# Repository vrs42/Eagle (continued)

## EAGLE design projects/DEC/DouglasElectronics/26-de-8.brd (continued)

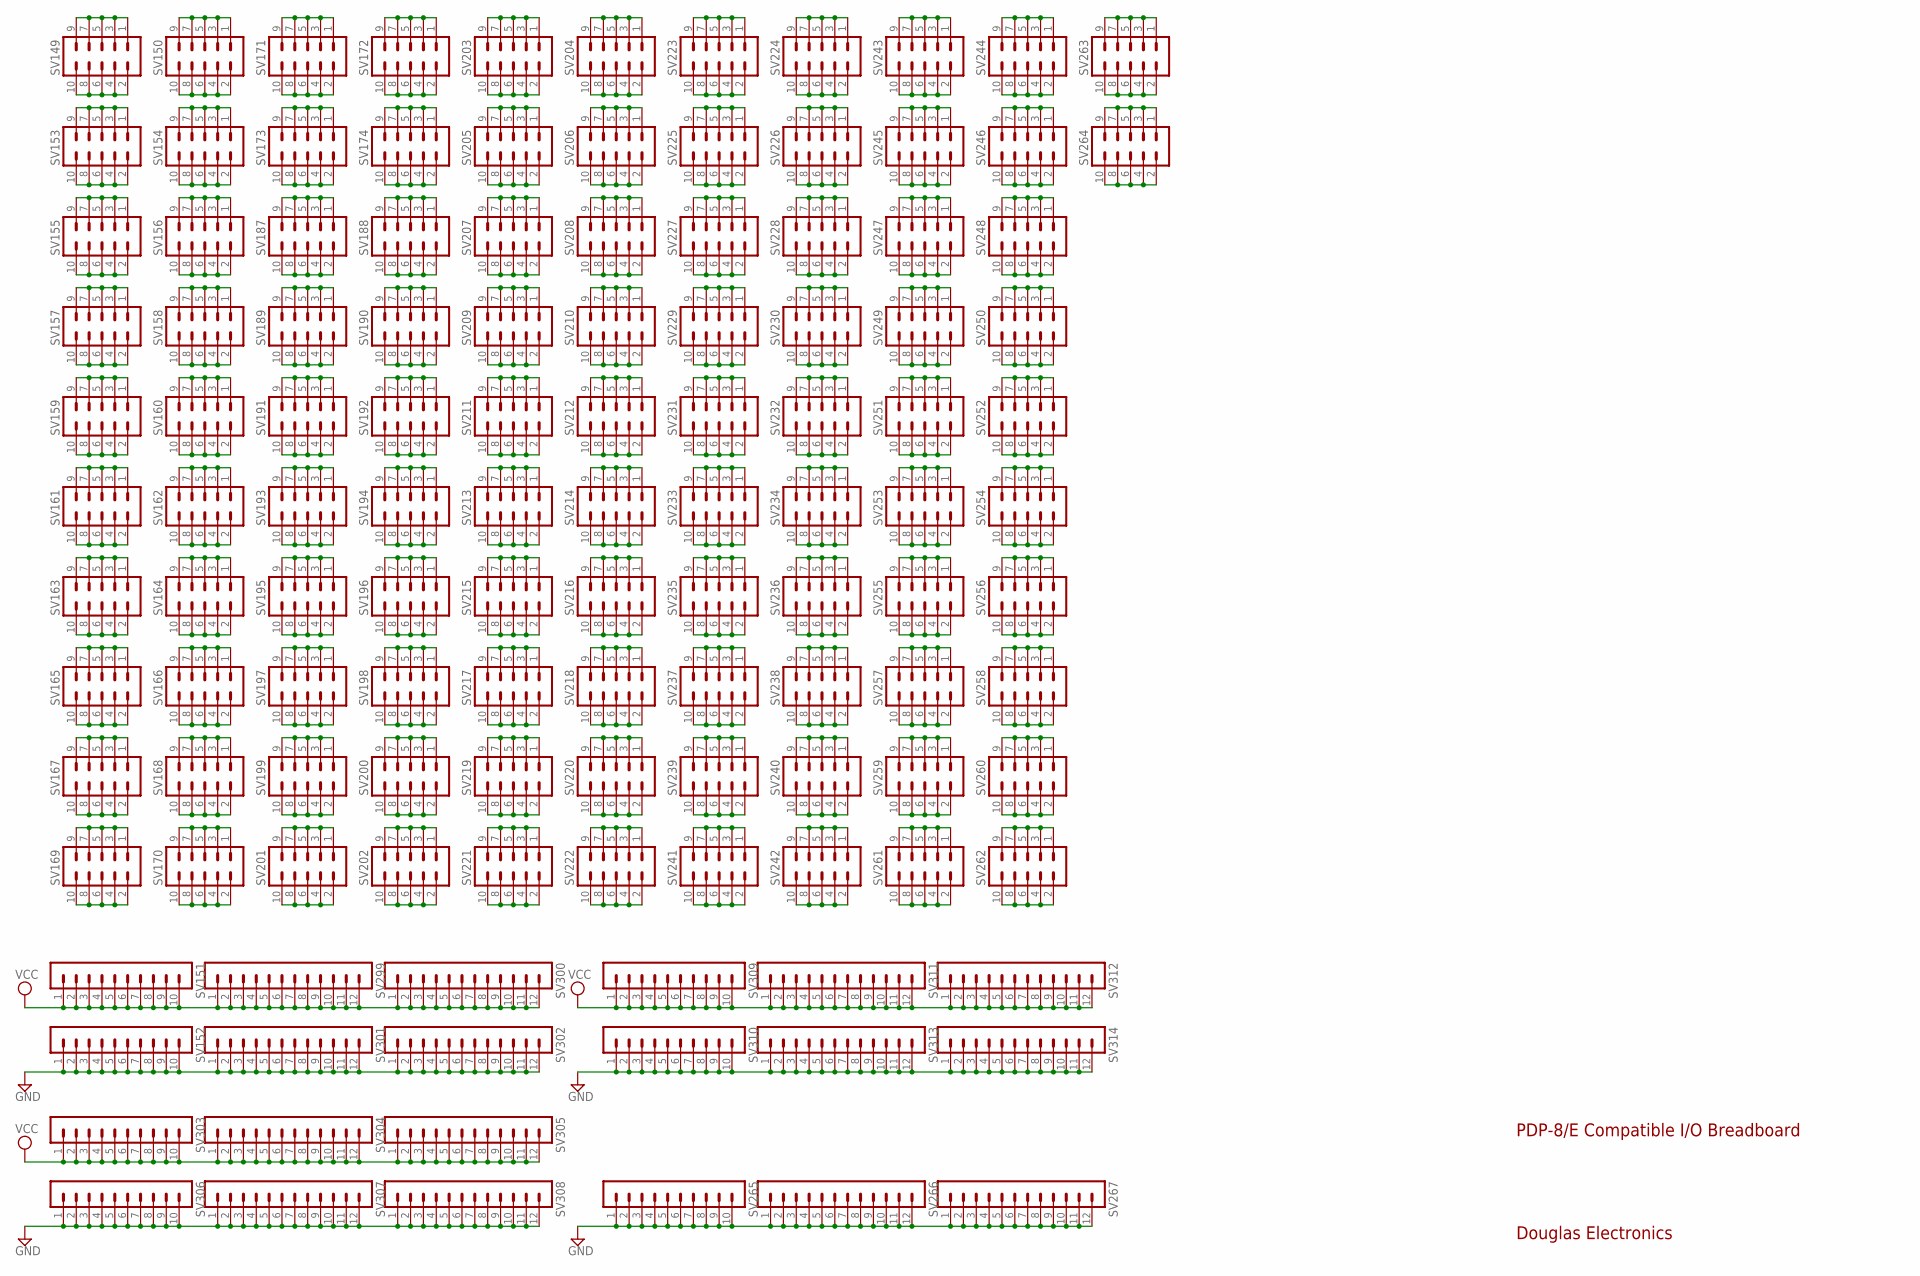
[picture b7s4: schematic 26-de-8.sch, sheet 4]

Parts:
SV149, SV150, SV153, SV154, SV155, SV156, SV157, SV158, SV159, SV160, SV161, SV162, SV163, SV164, SV165, SV166, SV167, SV168, SV169, SV170, SV171, SV172, SV173, SV174, SV187, SV188, SV189, SV190, SV191, SV192, SV193, SV194, SV195, SV196, SV197, SV198, SV199, SV200, SV201, SV202, SV203, SV204, SV205, SV206, SV207, SV208, SV209, SV210, SV211, SV212, SV213, SV214, SV215, SV216, SV217, SV218, SV219, SV220, SV221, SV222, SV223, SV224, SV225, SV226, SV227, SV228, SV229, SV230, SV231, SV232, SV233, SV234, SV235, SV236, SV237, SV238, SV239, SV240, SV241, SV242, SV243, SV244, SV245, SV246, SV247, SV248, SV249, SV250, SV251, SV252, SV253, SV254, SV255, SV256, SV257, SV258, SV259, SV260, SV261, SV262, SV263, SV264: MA05-2
SV151, SV152, SV265, SV303, SV306, SV309, SV310: MA10-1
SV266, SV267, SV299, SV300, SV301, SV302, SV304, SV305, SV307, SV308, SV311, SV312, SV313, SV314: MA12-1

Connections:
GND: SV152.1, SV152.2, SV152.3, SV152.4, SV152.5, SV152.6, SV152.7, SV152.8, SV152.9, SV152.10, SV265.1, SV265.2, SV265.3, SV265.4, SV265.5, SV265.6, SV265.7, SV265.8, SV265.9, SV265.10, SV266.1, SV266.2, SV266.3, SV266.4, SV266.5, SV266.6, SV266.7, SV266.8, SV266.9, SV266.10, SV266.11, SV266.12, SV267.1, SV267.2, SV267.3, SV267.4, SV267.5, SV267.6, SV267.7, SV267.8, SV267.9, SV267.10, SV267.11, SV267.12, SV301.1, SV301.2, SV301.3, SV301.4, SV301.5, SV301.6, SV301.7, SV301.8, SV301.9, SV301.10, SV301.11, SV301.12, SV302.1, SV302.2, SV302.3, SV302.4, SV302.5, SV302.6, SV302.7, SV302.8, SV302.9, SV302.10, SV302.11, SV302.12, SV306.1, SV306.2, SV306.3, SV306.4, SV306.5, SV306.6, SV306.7, SV306.8, SV306.9, SV306.10, SV307.1, SV307.2, SV307.3, SV307.4, SV307.5, SV307.6, SV307.7, SV307.8, SV307.9, SV307.10, SV307.11, SV307.12, SV308.1, SV308.2, SV308.3, SV308.4, SV308.5, SV308.6, SV308.7, SV308.8, SV308.9, SV308.10, SV308.11, SV308.12, SV310.1, SV310.2, SV310.3, SV310.4, SV310.5, SV310.6, SV310.7, SV310.8, SV310.9, SV310.10, SV313.1, SV313.2, SV313.3, SV313.4, SV313.5, SV313.6, SV313.7, SV313.8, SV313.9, SV313.10, SV313.11, SV313.12, SV314.1, SV314.2, SV314.3, SV314.4, SV314.5, SV314.6, SV314.7, SV314.8, SV314.9, SV314.10, SV314.11, SV314.12; also elsewhere on the board
unnamed: SV149.1, SV149.3, SV149.5, SV149.7, SV149.9
unnamed: SV149.2, SV149.4, SV149.6, SV149.8, SV149.10
unnamed: SV150.1, SV150.3, SV150.5, SV150.7, SV150.9
unnamed: SV150.2, SV150.4, SV150.6, SV150.8, SV150.10
unnamed: SV153.1, SV153.3, SV153.5, SV153.7, SV153.9
unnamed: SV153.2, SV153.4, SV153.6, SV153.8, SV153.10
unnamed: SV154.1, SV154.3, SV154.5, SV154.7, SV154.9
unnamed: SV154.2, SV154.4, SV154.6, SV154.8, SV154.10
unnamed: SV155.1, SV155.3, SV155.5, SV155.7, SV155.9
unnamed: SV155.2, SV155.4, SV155.6, SV155.8, SV155.10
unnamed: SV156.1, SV156.3, SV156.5, SV156.7, SV156.9
unnamed: SV156.2, SV156.4, SV156.6, SV156.8, SV156.10
unnamed: SV157.1, SV157.3, SV157.5, SV157.7, SV157.9
unnamed: SV157.2, SV157.4, SV157.6, SV157.8, SV157.10
unnamed: SV158.1, SV158.3, SV158.5, SV158.7, SV158.9
unnamed: SV158.2, SV158.4, SV158.6, SV158.8, SV158.10
unnamed: SV159.1, SV159.3, SV159.5, SV159.7, SV159.9
unnamed: SV159.2, SV159.4, SV159.6, SV159.8, SV159.10
unnamed: SV160.1, SV160.3, SV160.5, SV160.7, SV160.9
unnamed: SV160.2, SV160.4, SV160.6, SV160.8, SV160.10
unnamed: SV161.1, SV161.3, SV161.5, SV161.7, SV161.9
unnamed: SV161.2, SV161.4, SV161.6, SV161.8, SV161.10
unnamed: SV162.1, SV162.3, SV162.5, SV162.7, SV162.9
unnamed: SV162.2, SV162.4, SV162.6, SV162.8, SV162.10
unnamed: SV163.1, SV163.3, SV163.5, SV163.7, SV163.9
unnamed: SV163.2, SV163.4, SV163.6, SV163.8, SV163.10
unnamed: SV164.1, SV164.3, SV164.5, SV164.7, SV164.9
unnamed: SV164.2, SV164.4, SV164.6, SV164.8, SV164.10
unnamed: SV165.1, SV165.3, SV165.5, SV165.7, SV165.9
unnamed: SV165.2, SV165.4, SV165.6, SV165.8, SV165.10
unnamed: SV166.1, SV166.3, SV166.5, SV166.7, SV166.9
unnamed: SV166.2, SV166.4, SV166.6, SV166.8, SV166.10
unnamed: SV167.1, SV167.3, SV167.5, SV167.7, SV167.9
unnamed: SV167.2, SV167.4, SV167.6, SV167.8, SV167.10
unnamed: SV168.1, SV168.3, SV168.5, SV168.7, SV168.9
unnamed: SV168.2, SV168.4, SV168.6, SV168.8, SV168.10
unnamed: SV169.1, SV169.3, SV169.5, SV169.7, SV169.9
unnamed: SV169.2, SV169.4, SV169.6, SV169.8, SV169.10
unnamed: SV170.1, SV170.3, SV170.5, SV170.7, SV170.9
unnamed: SV170.2, SV170.4, SV170.6, SV170.8, SV170.10
unnamed: SV171.1, SV171.3, SV171.5, SV171.7, SV171.9
unnamed: SV171.2, SV171.4, SV171.6, SV171.8, SV171.10
unnamed: SV172.1, SV172.3, SV172.5, SV172.7, SV172.9
unnamed: SV172.2, SV172.4, SV172.6, SV172.8, SV172.10
unnamed: SV173.1, SV173.3, SV173.5, SV173.7, SV173.9
unnamed: SV173.2, SV173.4, SV173.6, SV173.8, SV173.10
unnamed: SV174.1, SV174.3, SV174.5, SV174.7, SV174.9
unnamed: SV174.2, SV174.4, SV174.6, SV174.8, SV174.10
unnamed: SV187.1, SV187.3, SV187.5, SV187.7, SV187.9
unnamed: SV187.2, SV187.4, SV187.6, SV187.8, SV187.10
unnamed: SV188.1, SV188.3, SV188.5, SV188.7, SV188.9
unnamed: SV188.2, SV188.4, SV188.6, SV188.8, SV188.10
unnamed: SV189.1, SV189.3, SV189.5, SV189.7, SV189.9
unnamed: SV189.2, SV189.4, SV189.6, SV189.8, SV189.10
unnamed: SV190.1, SV190.3, SV190.5, SV190.7, SV190.9
unnamed: SV190.2, SV190.4, SV190.6, SV190.8, SV190.10
unnamed: SV191.1, SV191.3, SV191.5, SV191.7, SV191.9
unnamed: SV191.2, SV191.4, SV191.6, SV191.8, SV191.10
unnamed: SV192.1, SV192.3, SV192.5, SV192.7, SV192.9
unnamed: SV192.2, SV192.4, SV192.6, SV192.8, SV192.10
unnamed: SV193.1, SV193.3, SV193.5, SV193.7, SV193.9
unnamed: SV193.2, SV193.4, SV193.6, SV193.8, SV193.10
unnamed: SV194.1, SV194.3, SV194.5, SV194.7, SV194.9
unnamed: SV194.2, SV194.4, SV194.6, SV194.8, SV194.10
unnamed: SV195.1, SV195.3, SV195.5, SV195.7, SV195.9
unnamed: SV195.2, SV195.4, SV195.6, SV195.8, SV195.10
unnamed: SV196.1, SV196.3, SV196.5, SV196.7, SV196.9
unnamed: SV196.2, SV196.4, SV196.6, SV196.8, SV196.10
unnamed: SV197.1, SV197.3, SV197.5, SV197.7, SV197.9
unnamed: SV197.2, SV197.4, SV197.6, SV197.8, SV197.10
unnamed: SV198.1, SV198.3, SV198.5, SV198.7, SV198.9
unnamed: SV198.2, SV198.4, SV198.6, SV198.8, SV198.10
unnamed: SV199.1, SV199.3, SV199.5, SV199.7, SV199.9
unnamed: SV199.2, SV199.4, SV199.6, SV199.8, SV199.10
unnamed: SV200.1, SV200.3, SV200.5, SV200.7, SV200.9
unnamed: SV200.2, SV200.4, SV200.6, SV200.8, SV200.10
unnamed: SV201.1, SV201.3, SV201.5, SV201.7, SV201.9
unnamed: SV201.2, SV201.4, SV201.6, SV201.8, SV201.10
unnamed: SV202.1, SV202.3, SV202.5, SV202.7, SV202.9
unnamed: SV202.2, SV202.4, SV202.6, SV202.8, SV202.10
unnamed: SV203.1, SV203.3, SV203.5, SV203.7, SV203.9
unnamed: SV203.2, SV203.4, SV203.6, SV203.8, SV203.10
unnamed: SV204.1, SV204.3, SV204.5, SV204.7, SV204.9
unnamed: SV204.2, SV204.4, SV204.6, SV204.8, SV204.10
unnamed: SV205.1, SV205.3, SV205.5, SV205.7, SV205.9
unnamed: SV205.2, SV205.4, SV205.6, SV205.8, SV205.10
unnamed: SV206.1, SV206.3, SV206.5, SV206.7, SV206.9
unnamed: SV206.2, SV206.4, SV206.6, SV206.8, SV206.10
unnamed: SV207.1, SV207.3, SV207.5, SV207.7, SV207.9
unnamed: SV207.2, SV207.4, SV207.6, SV207.8, SV207.10
unnamed: SV208.1, SV208.3, SV208.5, SV208.7, SV208.9
unnamed: SV208.2, SV208.4, SV208.6, SV208.8, SV208.10
unnamed: SV209.1, SV209.3, SV209.5, SV209.7, SV209.9
unnamed: SV209.2, SV209.4, SV209.6, SV209.8, SV209.10
unnamed: SV210.1, SV210.3, SV210.5, SV210.7, SV210.9
unnamed: SV210.2, SV210.4, SV210.6, SV210.8, SV210.10
unnamed: SV211.1, SV211.3, SV211.5, SV211.7, SV211.9
unnamed: SV211.2, SV211.4, SV211.6, SV211.8, SV211.10
unnamed: SV212.1, SV212.3, SV212.5, SV212.7, SV212.9
unnamed: SV212.2, SV212.4, SV212.6, SV212.8, SV212.10
unnamed: SV213.1, SV213.3, SV213.5, SV213.7, SV213.9
unnamed: SV213.2, SV213.4, SV213.6, SV213.8, SV213.10
unnamed: SV214.1, SV214.3, SV214.5, SV214.7, SV214.9
unnamed: SV214.2, SV214.4, SV214.6, SV214.8, SV214.10
unnamed: SV215.1, SV215.3, SV215.5, SV215.7, SV215.9
unnamed: SV215.2, SV215.4, SV215.6, SV215.8, SV215.10
unnamed: SV216.1, SV216.3, SV216.5, SV216.7, SV216.9
unnamed: SV216.2, SV216.4, SV216.6, SV216.8, SV216.10
unnamed: SV217.1, SV217.3, SV217.5, SV217.7, SV217.9
unnamed: SV217.2, SV217.4, SV217.6, SV217.8, SV217.10
unnamed: SV218.1, SV218.3, SV218.5, SV218.7, SV218.9
unnamed: SV218.2, SV218.4, SV218.6, SV218.8, SV218.10
unnamed: SV219.1, SV219.3, SV219.5, SV219.7, SV219.9
unnamed: SV219.2, SV219.4, SV219.6, SV219.8, SV219.10
unnamed: SV220.1, SV220.3, SV220.5, SV220.7, SV220.9
unnamed: SV220.2, SV220.4, SV220.6, SV220.8, SV220.10
unnamed: SV221.1, SV221.3, SV221.5, SV221.7, SV221.9
unnamed: SV221.2, SV221.4, SV221.6, SV221.8, SV221.10
unnamed: SV222.1, SV222.3, SV222.5, SV222.7, SV222.9
unnamed: SV222.2, SV222.4, SV222.6, SV222.8, SV222.10
unnamed: SV223.1, SV223.3, SV223.5, SV223.7, SV223.9
unnamed: SV223.2, SV223.4, SV223.6, SV223.8, SV223.10
unnamed: SV224.1, SV224.3, SV224.5, SV224.7, SV224.9
unnamed: SV224.2, SV224.4, SV224.6, SV224.8, SV224.10
unnamed: SV225.1, SV225.3, SV225.5, SV225.7, SV225.9
unnamed: SV225.2, SV225.4, SV225.6, SV225.8, SV225.10
unnamed: SV226.1, SV226.3, SV226.5, SV226.7, SV226.9
unnamed: SV226.2, SV226.4, SV226.6, SV226.8, SV226.10
unnamed: SV227.1, SV227.3, SV227.5, SV227.7, SV227.9
unnamed: SV227.2, SV227.4, SV227.6, SV227.8, SV227.10
unnamed: SV228.1, SV228.3, SV228.5, SV228.7, SV228.9
unnamed: SV228.2, SV228.4, SV228.6, SV228.8, SV228.10
unnamed: SV229.1, SV229.3, SV229.5, SV229.7, SV229.9
unnamed: SV229.2, SV229.4, SV229.6, SV229.8, SV229.10
unnamed: SV230.1, SV230.3, SV230.5, SV230.7, SV230.9
unnamed: SV230.2, SV230.4, SV230.6, SV230.8, SV230.10
unnamed: SV231.1, SV231.3, SV231.5, SV231.7, SV231.9
unnamed: SV231.2, SV231.4, SV231.6, SV231.8, SV231.10
unnamed: SV232.1, SV232.3, SV232.5, SV232.7, SV232.9
unnamed: SV232.2, SV232.4, SV232.6, SV232.8, SV232.10
unnamed: SV233.1, SV233.3, SV233.5, SV233.7, SV233.9
unnamed: SV233.2, SV233.4, SV233.6, SV233.8, SV233.10
unnamed: SV234.1, SV234.3, SV234.5, SV234.7, SV234.9
unnamed: SV234.2, SV234.4, SV234.6, SV234.8, SV234.10
unnamed: SV235.1, SV235.3, SV235.5, SV235.7, SV235.9
unnamed: SV235.2, SV235.4, SV235.6, SV235.8, SV235.10
unnamed: SV236.1, SV236.3, SV236.5, SV236.7, SV236.9
unnamed: SV236.2, SV236.4, SV236.6, SV236.8, SV236.10
unnamed: SV237.1, SV237.3, SV237.5, SV237.7, SV237.9
unnamed: SV237.2, SV237.4, SV237.6, SV237.8, SV237.10
unnamed: SV238.1, SV238.3, SV238.5, SV238.7, SV238.9
unnamed: SV238.2, SV238.4, SV238.6, SV238.8, SV238.10
unnamed: SV239.1, SV239.3, SV239.5, SV239.7, SV239.9
unnamed: SV239.2, SV239.4, SV239.6, SV239.8, SV239.10
unnamed: SV240.1, SV240.3, SV240.5, SV240.7, SV240.9
unnamed: SV240.2, SV240.4, SV240.6, SV240.8, SV240.10
unnamed: SV241.1, SV241.3, SV241.5, SV241.7, SV241.9
unnamed: SV241.2, SV241.4, SV241.6, SV241.8, SV241.10
unnamed: SV242.1, SV242.3, SV242.5, SV242.7, SV242.9
unnamed: SV242.2, SV242.4, SV242.6, SV242.8, SV242.10
unnamed: SV243.1, SV243.3, SV243.5, SV243.7, SV243.9
unnamed: SV243.2, SV243.4, SV243.6, SV243.8, SV243.10
unnamed: SV244.1, SV244.3, SV244.5, SV244.7, SV244.9
unnamed: SV244.2, SV244.4, SV244.6, SV244.8, SV244.10
unnamed: SV245.1, SV245.3, SV245.5, SV245.7, SV245.9
unnamed: SV245.2, SV245.4, SV245.6, SV245.8, SV245.10
unnamed: SV246.1, SV246.3, SV246.5, SV246.7, SV246.9
unnamed: SV246.2, SV246.4, SV246.6, SV246.8, SV246.10
unnamed: SV247.1, SV247.3, SV247.5, SV247.7, SV247.9
unnamed: SV247.2, SV247.4, SV247.6, SV247.8, SV247.10
unnamed: SV248.1, SV248.3, SV248.5, SV248.7, SV248.9
unnamed: SV248.2, SV248.4, SV248.6, SV248.8, SV248.10
unnamed: SV249.1, SV249.3, SV249.5, SV249.7, SV249.9
unnamed: SV249.2, SV249.4, SV249.6, SV249.8, SV249.10
unnamed: SV250.1, SV250.3, SV250.5, SV250.7, SV250.9
unnamed: SV250.2, SV250.4, SV250.6, SV250.8, SV250.10
unnamed: SV251.1, SV251.3, SV251.5, SV251.7, SV251.9
unnamed: SV251.2, SV251.4, SV251.6, SV251.8, SV251.10
unnamed: SV252.1, SV252.3, SV252.5, SV252.7, SV252.9
unnamed: SV252.2, SV252.4, SV252.6, SV252.8, SV252.10
unnamed: SV253.1, SV253.3, SV253.5, SV253.7, SV253.9
unnamed: SV253.2, SV253.4, SV253.6, SV253.8, SV253.10
unnamed: SV254.1, SV254.3, SV254.5, SV254.7, SV254.9
unnamed: SV254.2, SV254.4, SV254.6, SV254.8, SV254.10
unnamed: SV255.1, SV255.3, SV255.5, SV255.7, SV255.9
unnamed: SV255.2, SV255.4, SV255.6, SV255.8, SV255.10
unnamed: SV256.1, SV256.3, SV256.5, SV256.7, SV256.9
unnamed: SV256.2, SV256.4, SV256.6, SV256.8, SV256.10
unnamed: SV257.1, SV257.3, SV257.5, SV257.7, SV257.9
unnamed: SV257.2, SV257.4, SV257.6, SV257.8, SV257.10
unnamed: SV258.1, SV258.3, SV258.5, SV258.7, SV258.9
unnamed: SV258.2, SV258.4, SV258.6, SV258.8, SV258.10
unnamed: SV259.1, SV259.3, SV259.5, SV259.7, SV259.9
unnamed: SV259.2, SV259.4, SV259.6, SV259.8, SV259.10
unnamed: SV260.1, SV260.3, SV260.5, SV260.7, SV260.9
unnamed: SV260.2, SV260.4, SV260.6, SV260.8, SV260.10
unnamed: SV261.1, SV261.3, SV261.5, SV261.7, SV261.9
unnamed: SV261.2, SV261.4, SV261.6, SV261.8, SV261.10
unnamed: SV262.1, SV262.3, SV262.5, SV262.7, SV262.9
unnamed: SV262.2, SV262.4, SV262.6, SV262.8, SV262.10
unnamed: SV263.1, SV263.3, SV263.5, SV263.7, SV263.9
unnamed: SV263.2, SV263.4, SV263.6, SV263.8, SV263.10
unnamed: SV264.1, SV264.3, SV264.5, SV264.7, SV264.9
unnamed: SV264.2, SV264.4, SV264.6, SV264.8, SV264.10
VCC: SV151.1, SV151.2, SV151.3, SV151.4, SV151.5, SV151.6, SV151.7, SV151.8, SV151.9, SV151.10, SV299.1, SV299.2, SV299.3, SV299.4, SV299.5, SV299.6, SV299.7, SV299.8, SV299.9, SV299.10, SV299.11, SV299.12, SV300.1, SV300.2, SV300.3, SV300.4, SV300.5, SV300.6, SV300.7, SV300.8, SV300.9, SV300.10, SV300.11, SV300.12, SV303.1, SV303.2, SV303.3, SV303.4, SV303.5, SV303.6, SV303.7, SV303.8, SV303.9, SV303.10, SV304.1, SV304.2, SV304.3, SV304.4, SV304.5, SV304.6, SV304.7, SV304.8, SV304.9, SV304.10, SV304.11, SV304.12, SV305.1, SV305.2, SV305.3, SV305.4, SV305.5, SV305.6, SV305.7, SV305.8, SV305.9, SV305.10, SV305.11, SV305.12, SV309.1, SV309.2, SV309.3, SV309.4, SV309.5, SV309.6, SV309.7, SV309.8, SV309.9, SV309.10, SV311.1, SV311.2, SV311.3, SV311.4, SV311.5, SV311.6, SV311.7, SV311.8, SV311.9, SV311.10, SV311.11, SV311.12, SV312.1, SV312.2, SV312.3, SV312.4, SV312.5, SV312.6, SV312.7, SV312.8, SV312.9, SV312.10, SV312.11, SV312.12; also elsewhere on the board

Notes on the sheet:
PDP-8/E Compatible I/O Breadboard
Douglas Electronics

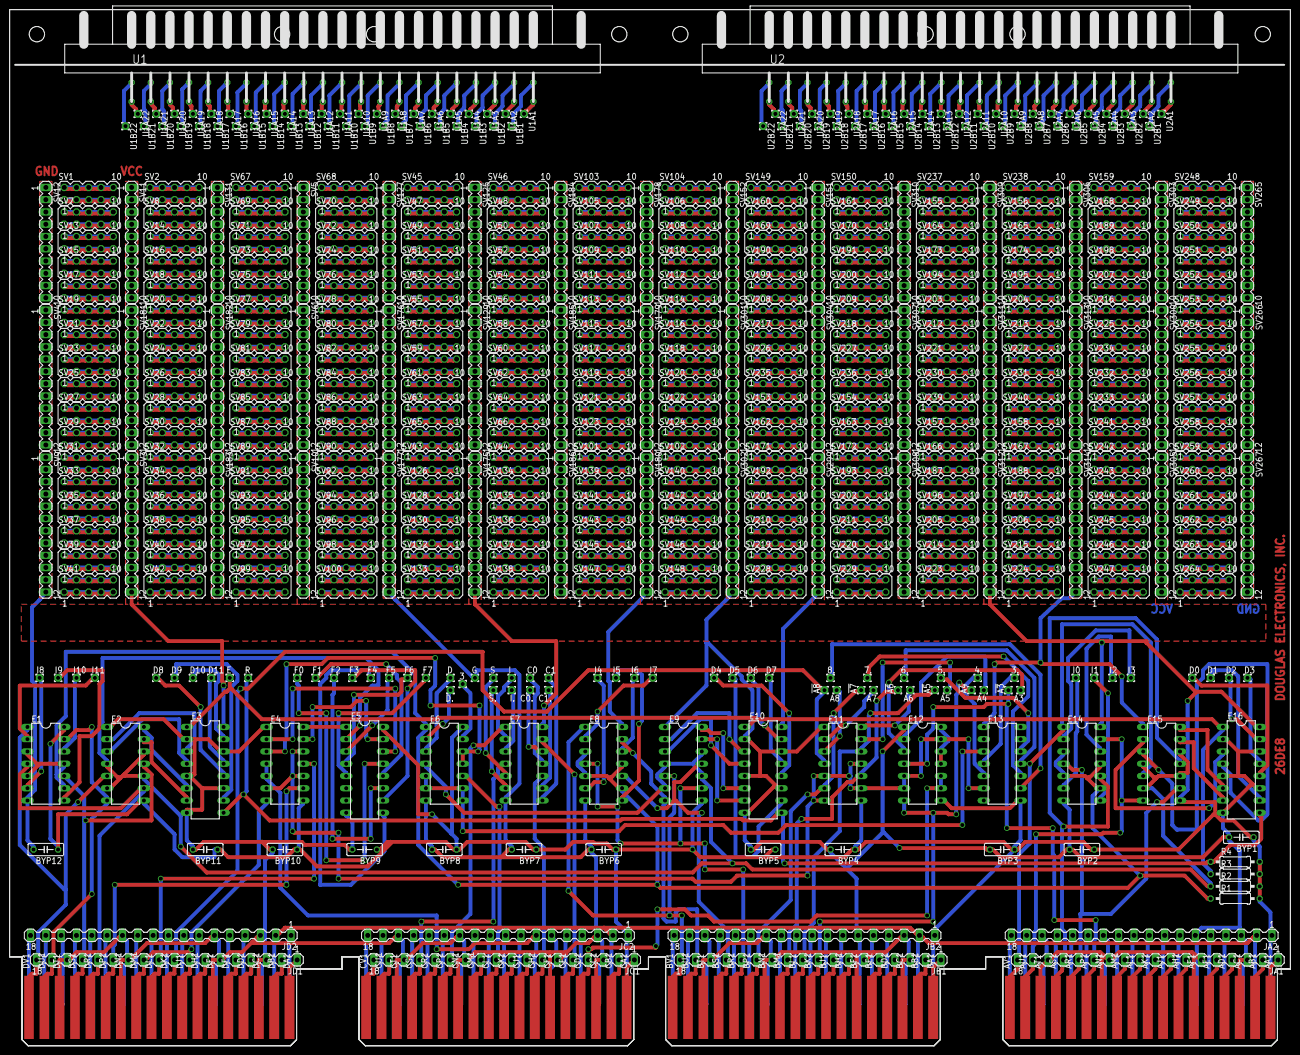
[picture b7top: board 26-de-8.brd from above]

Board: 2 copper layers, 265.3 x 214.6 mm, 479 parts (0 on the bottom side), 750 nets.
